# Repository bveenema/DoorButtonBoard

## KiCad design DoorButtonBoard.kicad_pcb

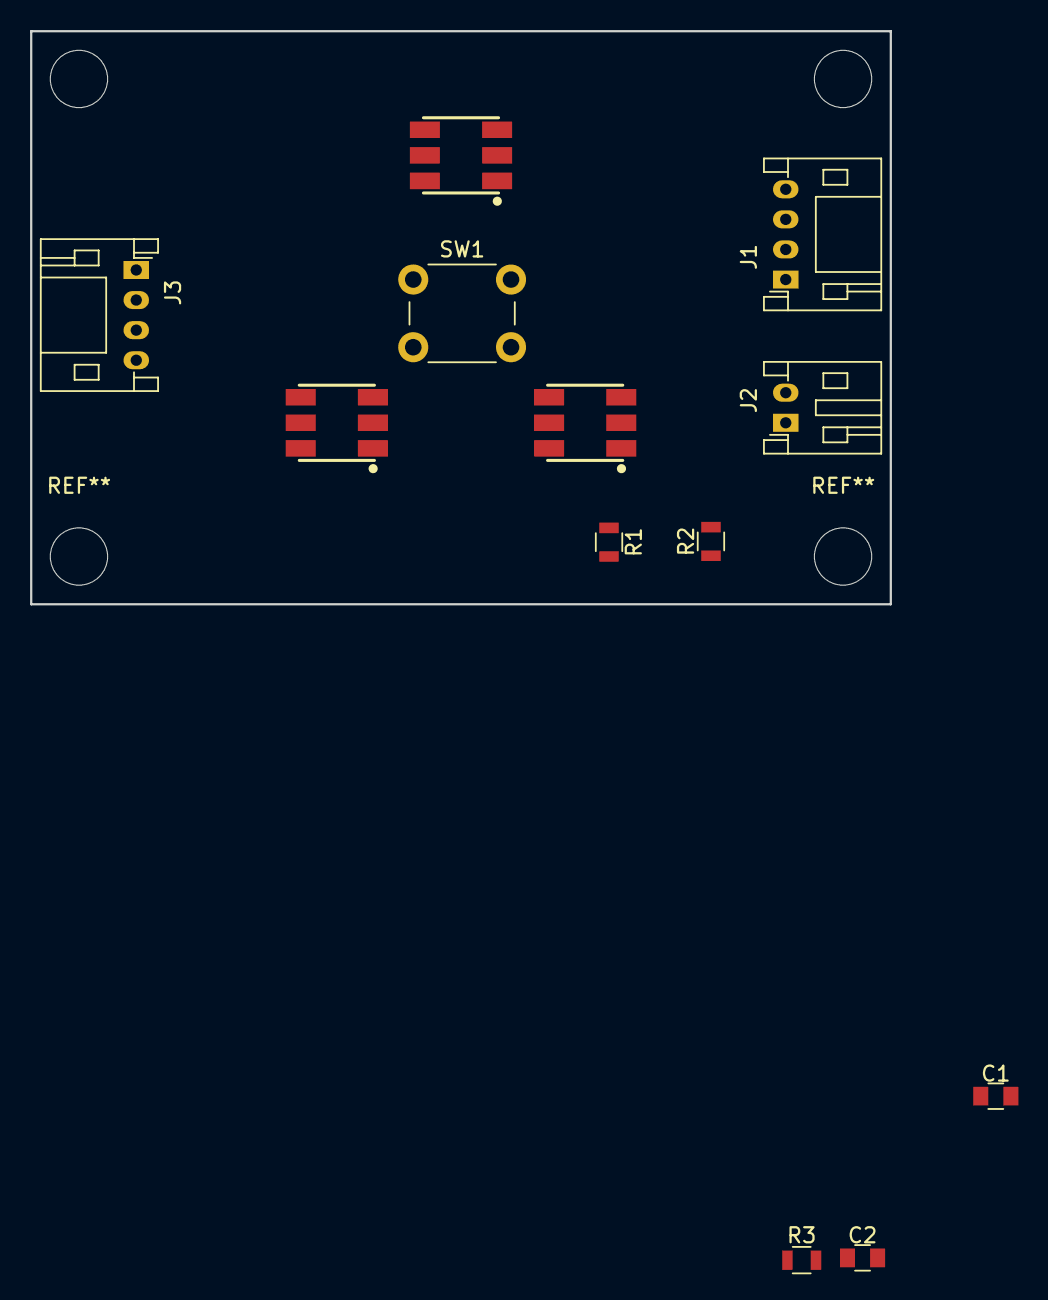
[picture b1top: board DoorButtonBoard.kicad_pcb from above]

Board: 2 copper layers, 57.2 x 38.1 mm, 12 parts (0 on the bottom side), 12 nets, no tracks yet.

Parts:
C1, C2: 0.1uF; C_0805
J1, J3: Conn_01x04; JST_PH_S4B-PH-K_04x2.00mm_Angled
J2: Conn_01x02; JST_PH_S2B-PH-K_02x2.00mm_Angled
R1: 1K; R_0805
R2: 2K; R_0805
R3: 51K; R_0805
SW1: SW_Push; SW_PUSH_6mm_h4.3mm
U1, U2, U3: APA102C; APA102_3

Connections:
+5V: C1.1, C2.1, J1.4, J3.1, R1.1, U1.4, U2.4, U3.4
/CI: J1.3, U1.2
/CO: J3.2, U3.5
/DI: J1.2, U1.1
/DO: J3.3, U3.6
GND: C1.2, C2.2, J1.1, J3.4, R2.2, R3.2, U1.3, U2.3, U3.3
unnamed: J2.1, R3.1, SW1.2
unnamed: R1.2, R2.1, SW1.1
unnamed: U1.5, U2.2
unnamed: U1.6, U2.1
unnamed: U2.5, U3.2
unnamed: U2.6, U3.1

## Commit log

2018-05-21 Initial Schematic and Lib
2018-05-21 Add Voltage Divider Values
2018-05-22 Complete Schematic and BOM, Start Layout
2018-05-22 Finish Rev A Layout, 3D and Gerber
2018-05-22 Finish Rev A
2018-05-23 Renamed files - Rev A
